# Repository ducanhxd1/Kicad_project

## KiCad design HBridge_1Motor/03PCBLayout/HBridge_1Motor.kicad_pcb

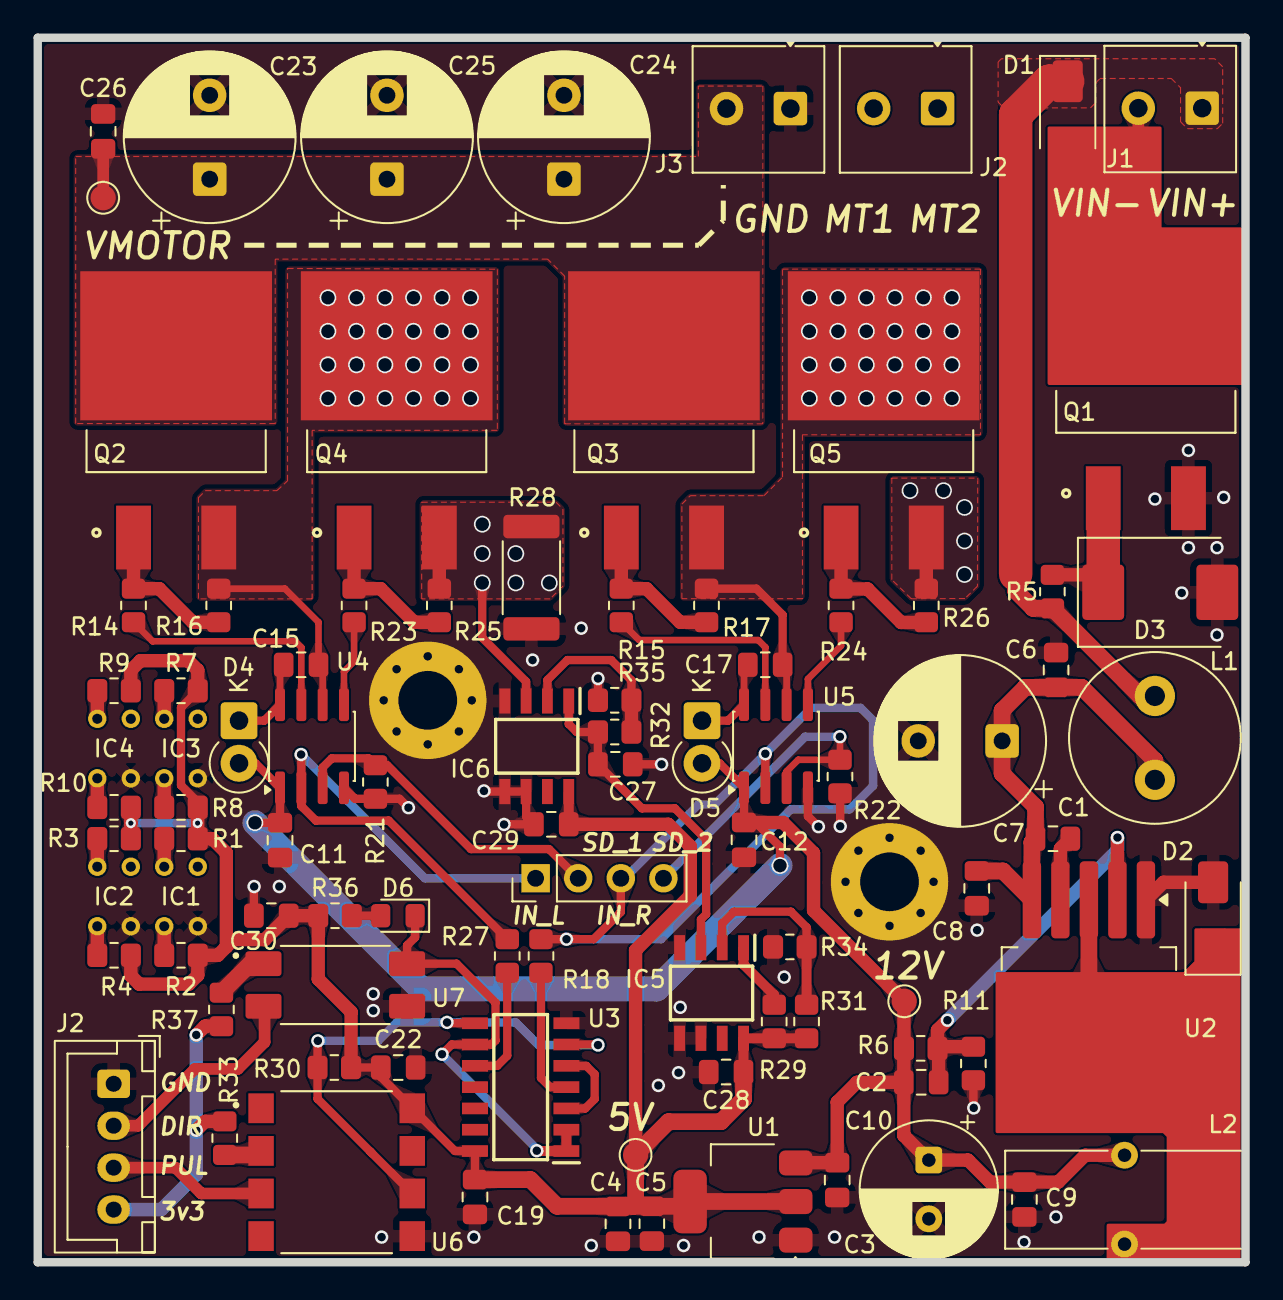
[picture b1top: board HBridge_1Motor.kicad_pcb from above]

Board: 2 copper layers, 72.0 x 73.0 mm, 90 parts (0 on the bottom side), 51 nets.

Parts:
C1, C8, C9, C15, C17: 105; C_0805_2012Metric_Pad1.18x1.45mm_HandSolder
C2: 33n; C_0805_2012Metric_Pad1.18x1.45mm_HandSolder
C3: 22u; C_0805_2012Metric_Pad1.18x1.45mm_HandSolder
C4: 10u; C_0805_2012Metric_Pad1.18x1.45mm_HandSolder
C5, C6, C11, C12, C19, C22, C28, C29, C30: 104; C_0805_2012Metric_Pad1.18x1.45mm_HandSolder
C7: 220uF/50V; CP_Radial_D10.0mm_P5.00mm
C10: 330uF/25V; CP_Radial_D8.0mm_P3.50mm
C23, C24, C25: 470uF/50V; CP_Radial_D10.0mm_P5.00mm
C26: 104/50V; C_0805_2012Metric_Pad1.18x1.45mm_HandSolder
C27: 10n; C_0805_2012Metric_Pad1.18x1.45mm_HandSolder
D1: SMAJ28A; D_SMA
D2: SS54F; D_SMA
D3: ZZM12; D_SMC
D4, D5: UF4007; D_DO-41_SOD81_P2.54mm_Vertical_CathodeUp
D6: LED; LED_0805_2012Metric_Pad1.15x1.40mm_HandSolder
IC1, IC2, IC3, IC4: GP1S093HCZ0F
IC5: LM393DR; SOIC127P600X175-8N
IC6: MCP6002-I_SN; SOIC127P600X175-8N
J1: +24V_Vin; TerminalBlock_Phoenix_MKDS-1-2-3.81_1x02_P3.81mm_Horizontal
J2: MOTOR; TerminalBlock_Phoenix_MKDS-1-2-3.81_1x02_P3.81mm_Horizontal
J2#2: Conn_01x04_Pin; JST_XH_B4B-XH-A_1x04_P2.50mm_Vertical
J3: V_Motor; TerminalBlock_Phoenix_MKDS-1-2-3.81_1x02_P3.81mm_Horizontal
L1: 4.7uH 5A; L_Radial_D10.0mm_P5.00mm_Neosid_SD12k_style3
L2: 47uH/5A; L_Toroid_Vertical_L14.0mm_W5.6mm_P5.30mm_Bourns_5700
Q1, Q2, Q3, Q4, Q5: IRF3205SPBF; TRANS_IRF3205SPBF
R1, R3, R5, R7, R9, R16, R17, R21, R22, R25, R26: 10K; R_0805_2012Metric_Pad1.20x1.40mm_HandSolder
R2, R4, R8, R10, R33, R37: 220; R_0805_2012Metric_Pad1.20x1.40mm_HandSolder
R6: 13K; R_0805_2012Metric_Pad1.20x1.40mm_HandSolder
R11: 1.5K; R_0805_2012Metric_Pad1.20x1.40mm_HandSolder
R14, R15, R23, R24: 22; R_0805_2012Metric_Pad1.20x1.40mm_HandSolder
R18, R27, R29: 4K7; R_0805_2012Metric_Pad1.20x1.40mm_HandSolder
R28: 0.02 (5W); R_2512_6332Metric_Pad1.40x3.35mm_HandSolder
R30: 3K3; R_0805_2012Metric_Pad1.20x1.40mm_HandSolder
R31: 2K; R_0805_2012Metric_Pad1.20x1.40mm_HandSolder
R32: 14K; R_0805_2012Metric_Pad1.20x1.40mm_HandSolder
R34: 3K; R_0805_2012Metric_Pad1.20x1.40mm_HandSolder
R35, R36: 1K; R_0805_2012Metric_Pad1.20x1.40mm_HandSolder
TP1: 12V; TestPoint_Pad_D1.5mm
TP2: 5V; TestPoint_Pad_D1.5mm
TP3: V_MOTOR; TestPoint_Pad_D1.5mm
U1: AMS1117-5.0; SOT-223-3_TabPin2
U2: XL4015; TO-263-5_TabPin3
U3: 4001; SOIC127P600X175-14N
U4, U5: IR2104; SOIC-8_3.9x4.9mm_P1.27mm
U6: 6N137; COUPL_6N138SDM
U7: PC817; SOIC254P960X420-4N

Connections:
3v3_MCU: J2#2.4, R33.1, R37.1
+5V: C4.1, C5.1, C19.1, C22.1, C28.1, C29.1, C30.1, IC5.8 (VCC), IC6.8 (VDD), R1.2, R2.2, R3.2, R4.2, R7.2, R8.2, R9.2, R10.2, R29.1, R30.2, R31.1, R36.2, TP2.1 (1_1), U1.2 (VO), U3.14 (VDD), U6.8 (VCC)
+12V: C2.1, C3.1, C9.1, C10.1, C11.1, C12.1, D4.2 (A), D5.2 (A), L2.2, R6.2, TP1.1 (1_1), U1.3 (VI), U4.1 (VCC), U5.1 (VCC)
+V_MOTOR: C23.1, C24.1, C25.1, C26.1, J3.2, Q2.2, Q3.2, TP3.1 (1_1)
DIR: D6.1 (K), U3.1, U3.2, U3.9, U7.4
DIR_MCU: J2#2.2, U7.2
FAULT: IC5.1 (1OUT), R29.2
GH_1: R14.1, U4.7 (HO)
GH_2: R15.1, U5.7 (HO)
GL_1: R23.1, U4.5 (LO)
GL_2: R24.1, U5.5 (LO)
GND: C3.2, C4.2, C5.2, C6.2, C7.2, C8.2, C9.2, C10.2, C11.2, C12.2, C19.2, C22.2, C23.2, C24.2, C25.2, C26.2, C27.2, C28.2, C29.2, C30.2, D2.2 (A), D3.2 (A), IC1.4 (CATHODE), IC2.4 (CATHODE), IC3.4 (CATHODE), IC4.4 (CATHODE), IC5.4 (GND), IC5.5 (2IN+), IC5.6 (2IN-), IC6.4 (VSS), IC6.5 (VINB+), IC6.6 (VINB-), J2#2.1, J3.1, Q1.3, R11.1, R21.1, R22.1, R28.2, R34.2, R35.2, U1.1 (GND), U2.1 (GND), U3.7 (VSS), U4.4 (COM), U5.4 (COM), U6.5 (GND), U7.3
IN_L: R27.2, U4.2 (IN)
IN_R: R18.2, U5.2 (IN)
MCU_ADC: C27.1, IC5.3 (1IN+), IC6.1 (VOUTA), R32.1
MOTOR1: C15.2, J2.2, Q2.3, Q4.2, R16.1, U4.6 (VS)
MOTOR2: C17.2, J2.1, Q3.3, Q5.2, R17.1, U5.6 (VS)
unnamed: D1.1 (A1), J1.1, L1.1, R5.1
unnamed: D1.2 (A2), J1.2, Q1.2
unnamed: D2.1 (K), L2.1, U2.3 (SW)
unnamed: D3.1 (K), Q1.1, R5.2
unnamed: C15.1, D4.1 (K), U4.8 (VB)
unnamed: C17.1, D5.1 (K), U5.8 (VB)
unnamed: D6.2 (A), R36.1
unnamed: IC1.1 (ANODE), R2.1
unnamed: IC1.2 (COLLECTOR), R1.1
unnamed: IC2.1 (ANODE), R4.1
unnamed: IC2.2 (COLLECTOR), R3.1
unnamed: IC3.1 (ANODE), R8.1
unnamed: IC3.2 (COLLECTOR), R7.1
unnamed: IC4.1 (ANODE), R10.1
unnamed: IC4.2 (COLLECTOR), R9.1
unnamed: IC5.2 (1IN-), R31.2, R34.1
unnamed: IC6.2 (VINA-), R32.2, R35.1
unnamed: Q2.1, R14.2, R16.2
unnamed: Q3.1, R15.2, R17.2
unnamed: Q4.1, R23.2, R25.2
unnamed: Q5.1, R24.2, R26.2
unnamed: R18.1, U3.4
unnamed: R27.1, U3.10
unnamed: R37.2, U7.1
unnamed: C2.2, R6.1, R11.2, U2.2 (FB)
unnamed: C1.2, U2.4 (VC)
unnamed: C1.1, C6.1, C7.1, C8.1, L1.2, U2.5 (VIN)
unnamed: U3.3, U3.5
unnamed: R33.2, U6.2 (A)
PULSE_MCU: J2#2.3, U6.3 (C)
PWM: R30.1, U3.6, U3.8, U6.6 (VO)
Rshunt: IC6.3 (VINA+), Q4.3, Q5.3, R25.1, R26.1, R28.1
SD_1: R21.2, U4.3 (~SD)
SD_2: R22.2, U5.3 (~SD)

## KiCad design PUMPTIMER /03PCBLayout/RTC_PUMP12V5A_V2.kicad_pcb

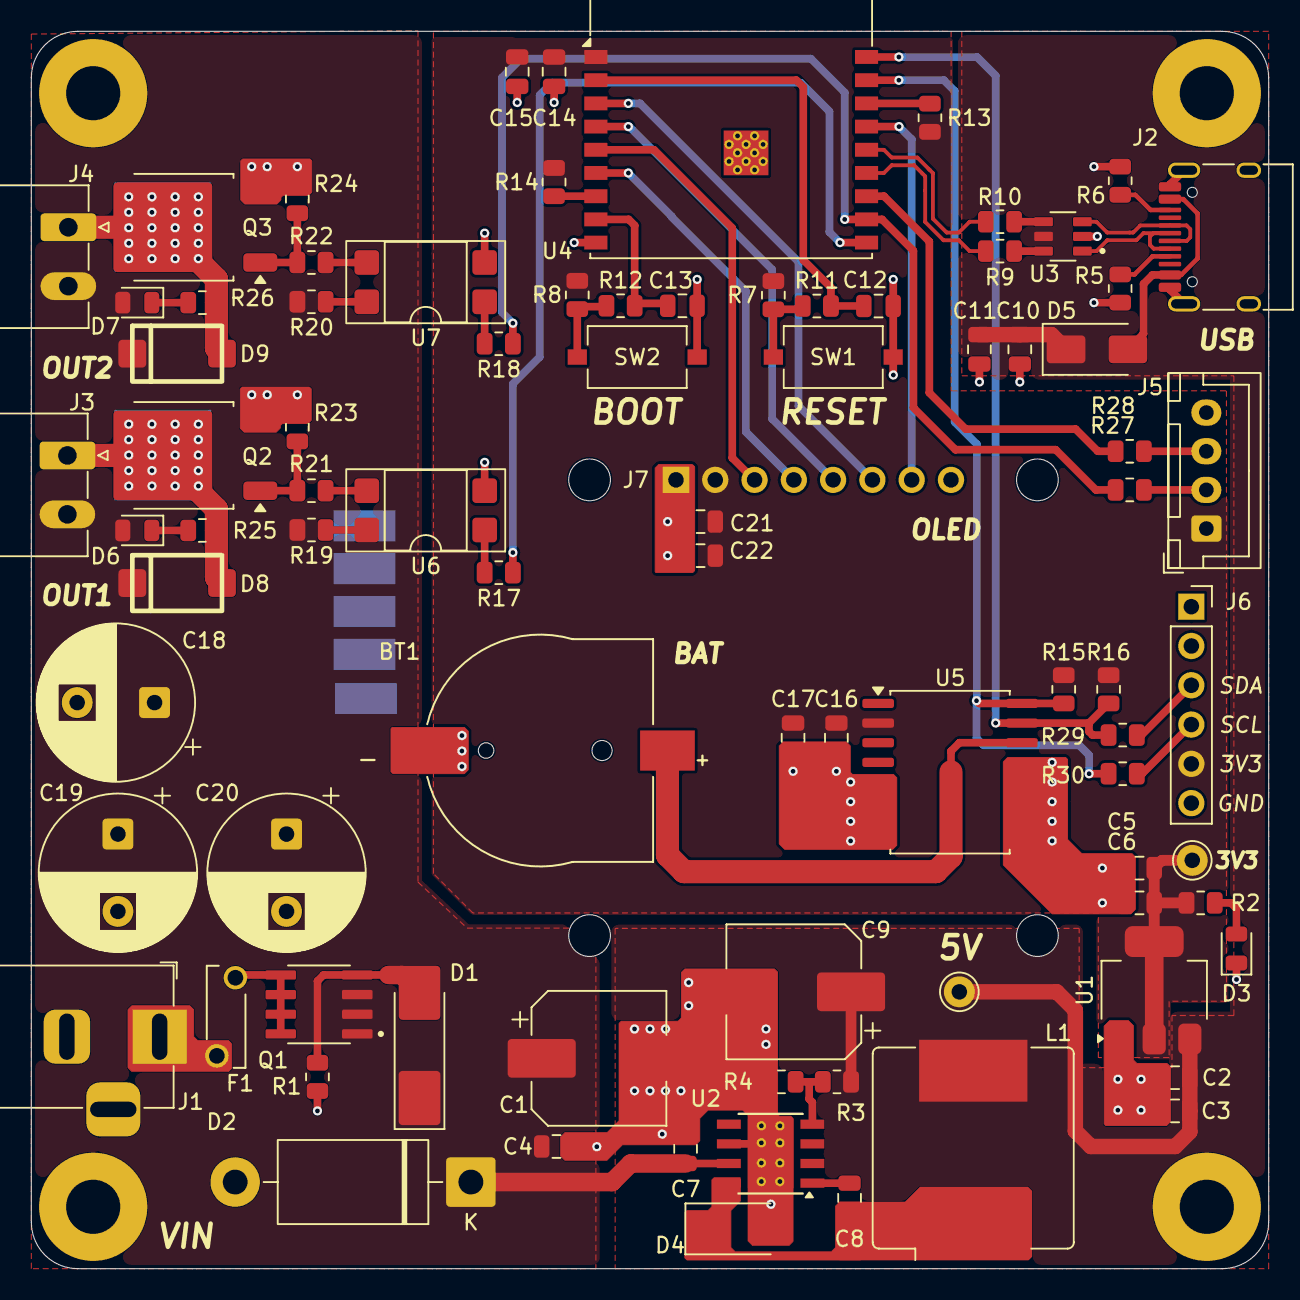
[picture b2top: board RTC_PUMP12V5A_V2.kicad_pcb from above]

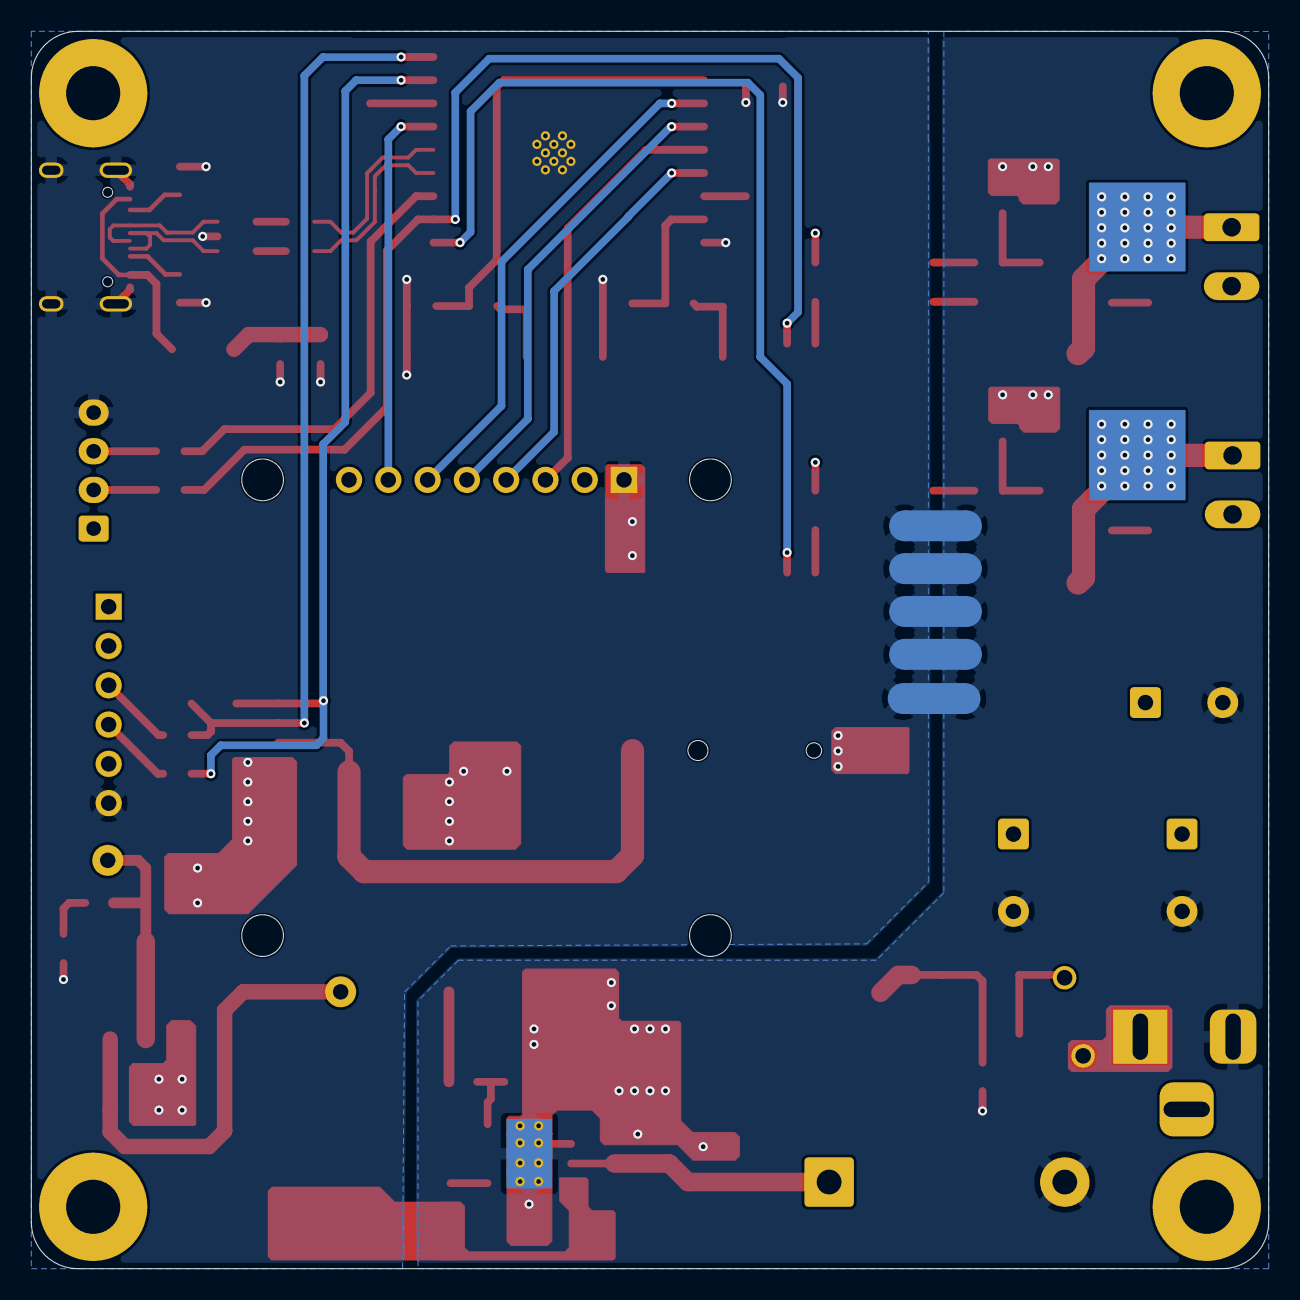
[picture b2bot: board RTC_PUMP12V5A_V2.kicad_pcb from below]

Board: 2 copper layers, 80.0 x 80.0 mm, 94 parts (5 on the bottom side), 54 nets.

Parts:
3V3, 5V: TestPoint; Pin_D1.0mm_L10.0mm
BT1: CH291-1220LF; CR1220
C1, C9: 220uF 35V; CP_Elec_8x10.5
C2, C5, C7, C10, C15, C17, C22: 10u; C_0805_2012Metric
C3, C4, C6, C11, C12, C13, C14, C16, C21: 100n; C_0805_2012Metric
C8: 0.01u; C_0805_2012Metric
C18, C19, C20: 470u; CP_Radial_D10.0mm_P5.00mm
D1: ZM4742A-GS08; D_MELF_Handsoldering
D2: 1.5KE15CA; D_DO-201AD_P15.24mm_Horizontal
D3, D6, D7: LED; LED_0805_2012Metric
D4, D5: SS34; D_SMA
D8, D9: SS54; Diode SS54
F1: RUEF700; FUSRR505W81L660T250H1360
H1, H2, H3, H4: MountingHole_Pad; MountingHole_3.5mm_Pad
J1: 12VDC_IN; BarrelJack_Horizontal
J2: USB_C_Receptacle_USB2.0_16P; USB_C_Receptacle_HRO_TYPE-C-31-M-12
J3, J4: Pump; PhoenixContact_MC_1,5_2-G-3.81_1x02_P3.81mm_Horizontal
J5: UART; JST_XH_B4B-XH-A_1x04_P2.50mm_Vertical
J6: Conn_01x06_Socket; PinSocket_1x06_P2.54mm_Vertical
J7: OLED SPI; Adafruit_SSD1306
L1: 33uH 4.2A; L_Bourns_SRR1208_12.7x12.7mm
NT1, NT2, NT3, NT4, NT5: NetTie_2; NetTie-2_SMD_Pad2.0mm
Q1: AO4407A; SOIC127P600X175-8N
Q2, Q3: IRLR7843; TO-252-2
R1, R3, R7, R8, R13, R14, R23, R24: 10k; R_0805_2012Metric
R2: 1k; R_0805_2012Metric
R4: 3k3; R_0805_2012Metric
R5, R6: 5k1; R_0805_2012Metric
R9, R10: 22; R_0805_2012Metric
R11, R12, R21, R22: 100; R_0805_2012Metric
R15, R16, R19, R20, R25, R26: 4k7; R_0805_2012Metric
R17, R18: 220; R_0805_2012Metric
R27, R28, R29, R30: 0R; R_0805_2012Metric
SW1, SW2: SW_Push; SW_Tactile_SPST_NO_Straight_CK_PTS636Sx25SMTRLFS
U1: LM1117MP-3.3; SOT-223-3_TabPin2
U2: TPS5430DDA; TI_SO-PowerPAD-8_ThermalVias
U3: USBLC6-2SC6; SOT95P280X145-6N
U4: ESP32-C3-WROOM-02
U5: DS3231M; SOIC-16W_7.5x10.3mm_P1.27mm
U6, U7: PC817; DIP-4_W7.62mm_SMDSocket_SmallPads

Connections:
5V: 5V.1 (1_1), C2.1, C3.1, C9.1, C10.1, C11.1, D5.1 (K), L1.2, R3.1, U1.3 (VI), U3.5
+3.3V: 3V3.1 (1_1), C5.1, C6.1, C14.1, C15.2, C16.1, C17.2, C21.1, C22.2, J5.1, J6.5, J7.2, R2.1, R7.2, R8.2, R13.2, R14.2, R15.2, R16.2, U1.2 (VO), U4.1 (3V3), U5.2 (VCC)
/MCU/D+: J2.A6 (D+), J2.B6 (D+), U3.3
/MCU/D-: J2.A7 (D-), J2.B7 (D-), U3.1
EN: C12.1, R11.2, U4.2 (EN)
GND: BT1.2, C2.2, C3.2, C5.2, C6.2, C10.2, C11.2, C12.2, C13.2, C14.2, C15.1, C16.2, C17.1, C21.2, C22.1, D3.1 (K), J2.A1 (GND), J2.A12 (GND), J2.B1 (GND), J2.B12 (GND), J2.SH (SHIELD), J5.4, J6.6, J7.1, NT1.2, NT2.2, NT3.2, NT4.2, NT5.2, R5.2, R6.2, SW1.1, SW2.1, U1.1 (GND), U3.2, U4.9 (GND), U4.19 (GND), U5.5 (GND), U5.6 (GND), U5.7 (GND), U5.8 (GND), U5.9 (GND), U5.10 (GND), U5.11 (GND), U5.12 (GND), U5.13 (GND)
GND_PWR: C1.2, C4.2, C7.2, C9.2, C18.2, C19.2, C20.2, D2.2 (A2), D4.2 (A), J1.2, NT1.1, NT2.1, NT3.1, NT4.1, NT5.1, Q2.3 (S), Q3.3 (S), R1.2, R4.2, R23.1, R24.1, U2.6 (GND), U2.9 (GNDPAD), U6.2, U7.2
IO0: R16.1, R29.1, U4.18 (IO0), U5.15 (SDA)
IO1: R15.1, R30.1, U4.17 (IO1), U5.16 (SCL)
IO2: R13.1, U4.16 (IO2)
IO3: J7.7, U4.15 (IO3)
IO4: J7.6, U4.3 (IO4)
IO5: J7.5, U4.4 (IO5)
IO6: J7.3, U4.5 (IO6)
IO7: J7.4, U4.6 (IO7)
IO8: R14.1, U4.7 (IO8)
IO9: C13.1, R12.2, U4.8 (IO9)
IO10: R17.1, U4.10 (IO10)
IO20: R18.1, R27.1, U4.11 (IO20/RXD)
IO21: R28.1, U4.12 (IO21/TXD)
unnamed: D1.2 (A), Q1.4, R1.1
unnamed: D3.2 (A), R2.2
unnamed: C8.1, D4.1 (K), L1.1, U2.8 (PH)
unnamed: D5.2 (A), J2.A4 (VBUS), J2.A9 (VBUS), J2.B4 (VBUS), J2.B9 (VBUS)
unnamed: D6.1 (K), R25.2
unnamed: D7.1 (K), R26.2
unnamed: D8.2 (A), J3.1, Q2.2 (D), R25.1
unnamed: D9.2 (A), J4.1, Q3.2 (D), R26.1
unnamed: F1.1, J1.1
unnamed: F1.2, Q1.5, Q1.6, Q1.7, Q1.8
unnamed: J2.A5 (CC1), R5.1
unnamed: J2.B5 (CC2), R6.1
unnamed: J5.2, R27.2
unnamed: J5.3, R28.2
unnamed: J6.3, R29.2
unnamed: J6.4, R30.2
unnamed: Q2.1 (G), R21.2, R23.2
unnamed: Q3.1 (G), R22.2, R24.2
unnamed: R9.1, U3.6
unnamed: R10.1, U3.4
unnamed: R7.1, R11.1, SW1.2
unnamed: R8.1, R12.1, SW2.2
unnamed: R17.2, U6.1
unnamed: R18.2, U7.1
unnamed: R19.1, U6.4
unnamed: R20.1, U7.4
unnamed: R21.1, U6.3
unnamed: R22.1, U7.3
unnamed: C8.2, U2.1 (BOOT)
unnamed: R3.2, R4.1, U2.4 (VSENSE)
unnamed: BT1.1, U5.14 (VBAT)
USB_D+: R10.2, U4.14 (IO19)
USB_D-: R9.2, U4.13 (IO18)
VIN: C1.1, C4.1, C7.1, C18.1, C19.1, C20.1, D1.1 (K), D2.1 (A1), D6.2 (A), D7.2 (A), D8.1 (K), D9.1 (K), J3.2, J4.2, Q1.1, Q1.2, Q1.3, R19.2, R20.2, U2.7 (VIN)
